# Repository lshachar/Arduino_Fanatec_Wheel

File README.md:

# Arduino_Fanatec_Wheel
A do-it-yourself steering wheel to Fanatec's wheel base.<br/><br/>
**29.10.2020** Run the project on a 3.3V Arduino without a logic shifter<br/>

[more info here](Pro%20Mini%20V2%203.3V/README.md)

*You can run the code on a 3.3V Arduino without the need for a logic shifter. This allows for a small enough pcb and 3D model to hold it, which you can then mount onto your custom wheel. Because the model is only 16mm high you won't have any space issues.
________________
**28.04.2020 Coronavirus update:** Version 1 is out!<br/>

[check out more photos here](https://github.com/lshachar/Arduino_Fanatec_Wheel/tree/master/Steering%20Wheel%20Photos)

*The buttons delay bug is fixed, buttons code is working great!<br/>
*I fixed several large bugs with the SPI communication, which now works flawlessly.<br/>
*Updated schematics - Added a 5 buttons Analog input that feeds into a single analog input on the arduino. You can calibrate your wheel center by using the D-pad and alphanumeric display, without plugging the Arduino to your PC!<br/>
*Added Diode, and connected D2 and D10 together, both changes are necessary! please revise your board to include these changes if you've built one already!<br/>
*Updated board layout - it's possible to either manufacture a single layer board, and solder a few jumper wires for the top layer, or manufacture the complete two-layers board. (I used a CNC machine and milled a single layer board)
________________

**This project is donationware, if my work helped you out** [**maybe get me a beer! :)**](https://paypal.me/lshachar)<br/><br/>
  
Fanatec's wheelbases won't enable any force feedback, unless you have a Fanatec steering wheel attached to it.
With this project, you can use an arduino to communicate with the wheelbase over SPI, which will get the wheelbase working.
You can attach buttons, a D-Pad and an alphanumeric display, for the complete package!

This simplified (schematics) version is enough to let you enable force feedback on your wheelbase,
[use this easy to understand 'breadboard view' simplified schematics](https://github.com/lshachar/Arduino_Fanatec_Wheel/blob/master/schamtics%20arduino%20nano-level%20shifter-fanatec%20round%20plug.png), or [This simplified schematic](https://github.com/lshachar/Arduino_Fanatec_Wheel/blob/master/schamtics%20arduino%20nano-level%20shifter-Simlified.png).

The full PCB supports alphanumeric display, D-pad, and lots of external buttons
 (I currently use 6: 2 paddle shifters and 4 buttons on the rim).

Here's a [how to make a male Fanatec SPI connector](Steering%20wheel%20connector%20-%20howto/Readme.md) (what the steering wheel has)<br/>
Also, [Alevale found where to buy the connector](https://github.com/darknao/btClubSportWheel/issues/14#issuecomment-604973137)<br/><br/>
[use this](3d%20Models/fanatec%20adapter%20v1.STL) If you need a simple 3d adapter to attach your physical steering wheel to the wheelbase<br/><br/>

### Several options:
- Use a 5V arduino with a logic level shifter. (recommended, this is what I use. [(here are The schematics)](https://github.com/lshachar/Arduino_Fanatec_Wheel/blob/master/schamtics%20arduino%20nano-level%20shifter-fanatec%20round%20plug.png)
- Use a 5V arduino **without** a logic shifter (can be risky to your precious wheelbase)
- Use a 3.3V arduino (You will need an Arduino Pro Mini V2 which runs 3.3V at 16 MHz, as 8 MHz is not fast enough. For a more detailed guide [please read this](Pro%20Mini%20V2%203.3V/README.md))

Code was tested on arduino Uno and Nano, and works fine. However, they both output 5V and the SPI communication on the wheelbase
is using 3.3V.
It's best to use a level shifter between the two, so there are no chances of damaging the wheelbase (by connecting the 5V arduino 
output to a 3.3V wheelbase input)
However, since the wheelbase is the master and the steering wheel is the slave - MISO is the only *input* channel on the wheelbase,
and it is safe to simply use a voltage divider on the MISO line - to go from 5V level to 3.3V. (The arduino should recognize the 3.3V input signals coming from the wheelbase as high, so there's nothing we have to do there). <br/>
- **Note:** If you do end up going this route, make sure you wire everything up properly, and that you never set SPI as master on the arduino, or you will subject the wheelbase SPI to 5V. (I did subject the wheelbase SPI to 5V by mistake - and nothing got damaged.)<br/><br/>

I recommend using an arduino nano **and** a logic shifter, as seen in the schematics.
- **Note:** The diode is crucial to keep the 5V coming from the wheelbase, and the 5V coming from the computer USB, seperate. the diode will drop the 5V voltage from the wheelbase to ~4.3V, which is fine for the arduino to run on. When you plug the USB cable, the arduino will run on the 5V coming from the computer, and current cannot flow to the wheelbase because of the diode.<br/>
fyi I have connected both power supplies together, and did not have anything go up in smoke. (but this is before I thought about using a diode. DO NOT ATTEMPT THIS YOURSELF.<br/>

[There's a lot of (old) info here](https://github.com/darknao/btClubSportWheel/issues/12)

# What to do if you gotta calibrate your wheelbase center?
On some wheelbases, you can do that directly from the [Fanatec wheel properties page](https://github.com/lshachar/Arduino_Fanatec_Wheel/issues/7). unfortunately it doesn't work on my CSW V2.5.<br/>
You can use the current code to calibrate the wheelbase's center point. (This is needed after a firmware upgrade for the wheelbase) the arduino will translate the alphanumeric display to letters and send them out to the Serial monitor(!). you will need to type in some commands on the Serial monitor, which will look pretty cypheric to you.
Type these characters on the serial monitor, press [return] after each line: <br/><br/>
C		(to change bits on the 3rd byte that affects buttons. C=3rd)
6		(to change (raise) the sixth bit on the 3rd byte, which is the menu button. this will cause the alphanumeric display to turn on and the message '5_1' (equivilent to 'S_1' i.e. 'setting 1') will be printed on the serial monitor.)  
6		(to release the menu button (lower the 6th bit) )  
23		(2 will raise the D-pad button bit, 3 will raise the joystick button bit.)  
23		(to release both buttons, drop both bits)
6		(press the menu button again to exit the menu)  
6		(release the menu button)  
[Watch this If you don't know what I'm talking about](https://www.youtube.com/watch?v=yvhAKxjit8o)  
(Hey - it's not an easy procedure, but it works!)
if you made a PCB with a Dpad and alphanumeric display - you can calibrate the center point without connecting to the computer!
Using the Dpad:
Enter the menu by pressing both up+down bubttons on the Dpad,
S_1 will appear on the serial monitor and on the alphanumeric display,
Press both left+right buttons on the Dpad to calibrate wheel center,
Press both up+down on the Dpad to exit menu. Done!

This project would never have been possible without the work of Darknao on his [BtClubSportWheel - converting any Fanatec CSW steering wheel to a standalone USB version](https://github.com/darknao/btClubSportWheel) project.

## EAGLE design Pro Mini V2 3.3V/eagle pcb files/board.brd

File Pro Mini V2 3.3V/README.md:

# Pro Mini V2 3.3V 16 MHz
What you'll need:
* Fanatec QR
* [Pro Mini V2](https://www.ebay.com/itm/Enhancement-V2-Pro-Mini-328-16Mhz-3-3V-5V-adjustable-Arduino-Compatible-40Pins/324180291509?hash=item4b7aa6afb5:g:~UgAAOxymiVQ~6z~)
* FTDI Adapter USB to TTL Programmer
* PCB [can be found here](eagle%20pcb%20files/Gerber.zip)
  * upload `Gerber.zip` to a PCB service like JLCPCB and order them
* 6x M5x20mm countersunk screws (e.g. DIN 7991)

optional:
* 8 pin JST connector
* 2x M2.5 screws to secure the pcb to the 3D model

# How To
* Make sure that the solder bridge on the Pro Mini is set to 3.3V
* uncomment following lines:
  * `#define HAS_TM1637_DISPLAY` - we are not using the TM1637 display module
  * `#define HAS_ANALOG_DPAD` - otherwise the funky switch is constantly pressed
* Program the Pro Mini using the option ATmega328P (5V, 16 MHz)
* Mark the cable coming from the QR which is 5V
* Solder the cables onto the pcb. Make sure that the marked cable (5V) is aligned with the 5V PCB pin
  * You can either solder the wires coming from the Fanatec QR directly to the PCB (recommended) or use an 8 pin JST connector so you can plug the cables coming from the QR into it
  * I had connection problems using the JST connector as the cable did not stick in correctly all the time, so I just soldered the wires and everything worked fine afterwards.
* Bend the cable so that it fits into the QR housing like so:

* Take the 3D printed QR adapter, put two M2.5 screws into each hole to secure the pcb
* Make sure that the cable is not squeezed and use the six M5 screws to mount it to the Fanatec QR
* Done!

# Warning
If you ever connect the FTDI to the board while also having it connected to the wheelbase **make sure to remove the VCC pin on the FTDI interface**, otherwise it might **damage your wheelbase** because this will connect the 3.3V coming from the FTDI with the 3.3V of the wheelbase.

# Downsides
* In some rare cases my base reconnects if I connect the emulator to it. Nothing wild, just let it recalibrate and you're ready to race

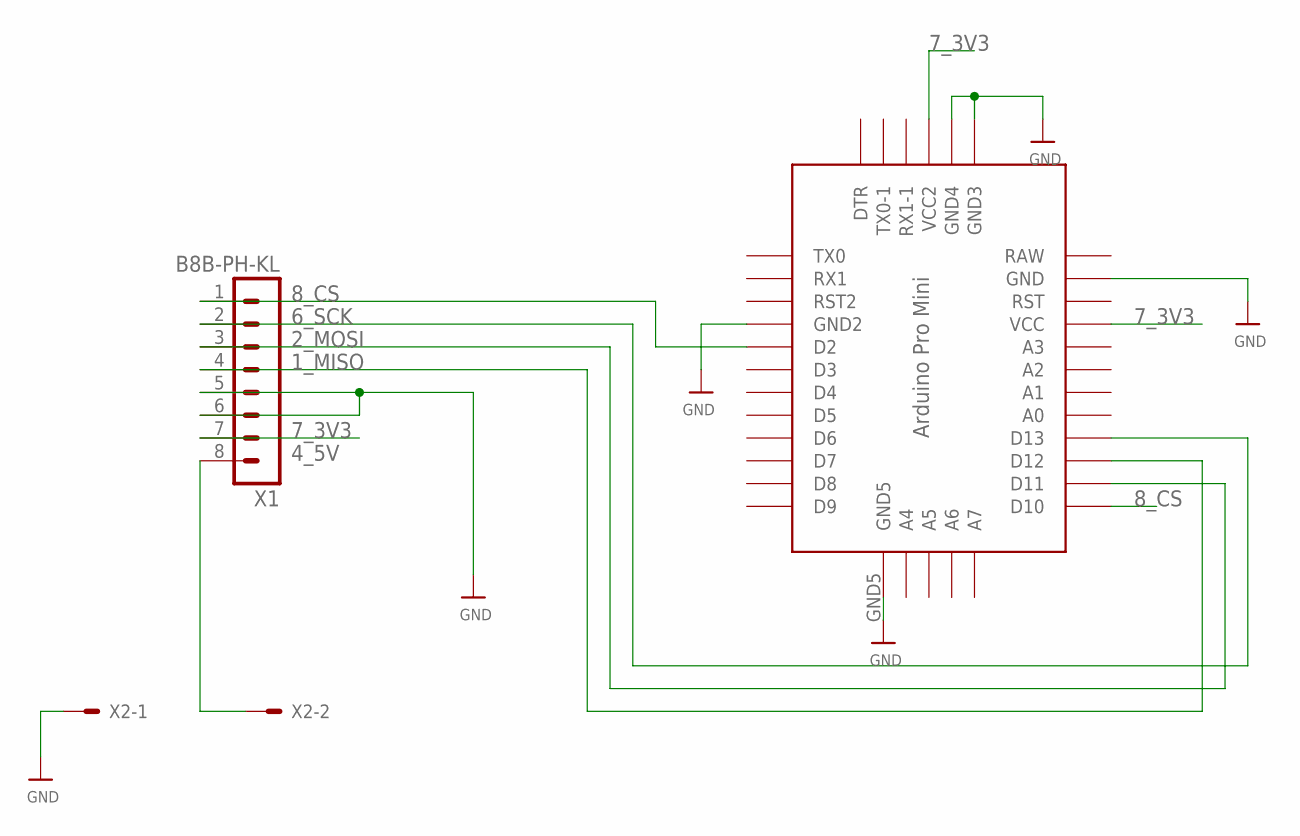
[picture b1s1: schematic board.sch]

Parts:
U$7: PRO-MINI_5BOT; PRO-MINI-5BOT
X1: B8B-PH-KL; B8B-PH-K-S
X2: 87758-0216

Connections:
1_MISO: U$7.D12, X1.4
2_MOSI: U$7.D11, X1.3
4_5V: X1.8, X2.2
6_SCK: U$7.D13, X1.2
7_3V3: U$7.VCC, U$7.VCC2, X1.7
8_CS: U$7.D2, U$7.D10, X1.1
GND: U$7.GND, U$7.GND2, U$7.GND3, U$7.GND4, U$7.GND5, X1.5, X1.6, X2.1
RAW: U$7.RAW

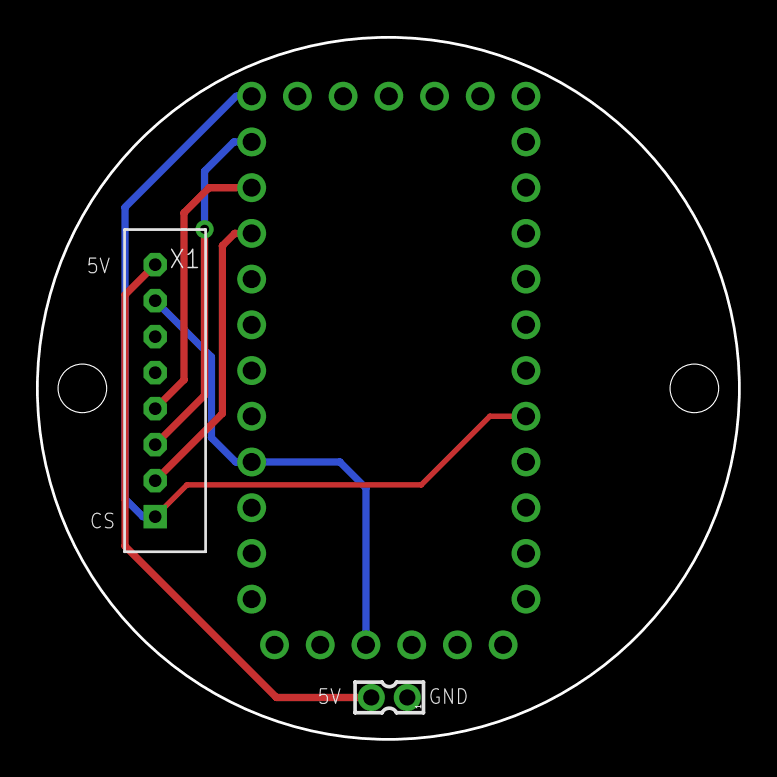
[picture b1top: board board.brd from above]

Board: 2 copper layers, 39.0 x 39.0 mm, 3 parts (0 on the bottom side), 7 nets.

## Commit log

2019-07-01 Debug code: for some reason when a button is sent, it roughly takes 170ms before it appears in windows. however, the button disappears instantly when that command is sent. connect a buzzer (piezoelec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
2019-07-03 left + right peddals
2019-07-03 FanatecWindowsDisplay init commit
2019-07-03 fix alphanumeric display bug regarding characters that did not change
2019-07-03 This little test helped me make sure that the wheelbase raises the CS line after every time that the buffer is completely read out. (ie if buffer gets read 10 times, CS line will raise 10 times). So 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
2019-07-03 implemented a buffer for the returnData array: when clicking a button there is an ~180 ms delay before the computer receives the command. I thought that buffering the buttons and the crc8 before send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
2019-09-15 readme - arduino nano tested
2019-10-05 Simple schematics to show the connection between Fanatec's round wheelbase plug, a logic shifter, and an Arduino nano. Credit to Jonbakhol
2019-12-31 new schematics and pcb layout. To be manufactured from a single layer board (bottom only). Top can easily be connected with some pieces of wire. (in the 3d screenshot file, the bottom layer is displa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
2019-12-31 Display support: TM1637 chip, 7 segments 4 digits display (only 3 digits are used). buy the display version that has decimal dots next to each digit!
2019-12-31 Added schematics and PCB (work in progress) with 7 segments display and Dpad+menu buttons. Thinking about connecting all these buttons to one analog input, but reading analog inputs takes longer. OTO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
2020-04-10 The PCB now supports the 4 digits alphanumeric display and 5 buttons D-pad, which are read by a single analog pin on the arduino. see README.md in schematics & pcb layout for more information about t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
2020-04-13 debugging the cable select pin
2020-04-13 button debugging, for digital / analog buttons that are each connected to a single input on the arduino (with internal input pullup, and ground connection)
2020-04-13 working nicely
2020-04-27 Cleanup
2020-04-27 print dpad value on alphanumeric display - nicer & simpler
2020-04-27 buttons and Dpad code now uses sensible functions
2020-04-28 updated PCB layout and schematics, including Dpad, Alphanumeric display, buttons, Diode - and many bug fixes
2020-11-01 Closes #9 Update readme, provide images, pcb and 3d qr adapter model
2020-11-15 #9 Update readme and PCB files
    - add wheelbase damage warning
    - add note to uncomment lines
    - remove connection of 5V to RAW (including diode)
2022-03-13 see https://github.com/lshachar/Arduino_Fanatec_Wheel/issues/20
2022-12-19 Updated the PCB front silkscreen, exported Geber files for manufacturing according to jlcpcb's requirements
2023-01-04 new: "CRC8 Match" messages will be generated on the serial connection, for easier debugging of the SPI interface, which is the issue most users experience. I am getting somewhere between 10 to 200 "m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
2023-01-04 bug solved (with debug code)
2023-01-04 Fixing alphanumeric display jittering: when packet was received with a bad crc8, do not display the text on the alphanumeric display. For the serial monitor, you can uncomment the line: #define DISPL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
